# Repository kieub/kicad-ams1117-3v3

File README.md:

# AMS1117-3.3 Ultra-Compact LDO Power Module

KiCad를 활용하여 설계하고 JLCPCB를 통해 제작한 초소형 3.3V LDO 전원 레귤레이터 모듈입니다.  
5V~12V 입력을 받아 MCU, 센서 및 통신 모듈 구동에 필요한 저노이즈 3.3V 전원을 공급합니다.

---

## 1. 주요 사양 (Specifications)

| 항목 | 사양 (Specifications) | 비고 |
| :--- | :--- | :--- |
| **Topology** | Linear LDO Regulator | 저노이즈 3.3V 전원 출력 |
| **Input Voltage ($V_{in}$)** | DC 4.75V ~ 12V | 권장 입력 전압: 5V |
| **Output Voltage ($V_{out}$)** | DC 3.3V (±1.5%) | 고정 출력 (Fixed Output) |
| **Max Output Current ($I_{out}$)** | Max 800mA | 입력 전압 및 방열 조건에 따라 상이 |
| **PCB Dimensions** | 23.75 mm × 11.5 mm (1.6T) | 초소형 2-Layer FR-4 |
| **Surface Finish** | HASL (with lead) | 0805 수동 납땜성(Wettability) 최적화 |
| **Interface** | Wire Direct Soldering Pad | 실장 높이 최소화 및 기구 매립형 |

---

## 2. 부품 구성표 (BOM: Bill of Materials)

| Reference | Component / Part Number | Package | Description | Qty |
| :--- | :--- | :--- | :--- | :--- |
| **U1** | AMS1117-3.3V | SOT-223 | 3.3V 800mA LDO Regulator | 1 |
| **C1, C2** | 10µF / 25V (CL21A106KAFN3NE) | 0805 | 입·출력 평활 MLCC (DC 바이어스 마진 확보) | 2 |
| **R1** | 1kΩ ±1% 125mW (ERJ6ENF1001V) | 0805 | 상태 표시 LED 전류 제한 저항 | 1 |
| **D1** | Red-Orange SMD LED (599-0120-007F) | 0805 | 전원 인디케이터 LED ($I_f \approx 1.3\text{mA}$) | 1 |

---

## 3. 핵심 설계 포인트 (Engineering Points)

- **BOM 최적화 및 DC 바이어스 마진 확보**: 입·출력 평활 커패시터를 25V 내압의 10µF 0805 MLCC 1종으로 통합하여 자재 조달 효율을 극대화하고, DC 바이어스 전압 인가에 따른 실효 커패시턴스 감소 현상을 방지했습니다.
- **저전력 LED 회로 설계**: 3.3V 출력단에 1kΩ 저항을 직렬 매칭하여 약 1.3mA의 저전류 구동을 유도, 불필요한 대기 전력 소모와 눈부심을 줄였습니다.
- **방열 및 소형화 설계**: SOT-223 탭 하단에 넓은 구리 배선을 배치하여 열 방출 경로를 확보했으며, 커넥터 대신 와이어 직결 패드를 채택해 완제품 매립 시 부피를 최소화했습니다.

---

## 4. 디렉터리 구조 (Directory Structure)

```text
├── docs/               # 회로도, PCB 3D 렌더링, 실물 사진
├── gerber/             # JLCPCB 양산 발주용 거버 파일 (ZIP)
├── hardware/           # KiCad 프로젝트 파일 (.kicad_pro, .kicad_sch, .kicad_pcb)
└── README.md
```

---

## 5. 제작 및 검증 가이드 (Assembly & Verification)

### 5.1 실장 전 기판 검수 (Bare Board Inspection)
- **외관 검사**: 거버 파일과 실물 PCB를 대조하여 트레이스 단선, 비아 도금 상태, 솔더마스크 오픈 영역을 육안 점검합니다.
- **전원단 도통 검사**: 부품 실장 전 멀티미터 도통 모드로 $V_{in}\text{-}GND$ 및 $V_{out}\text{-}GND$ 간 단락(Short)이 없는지 확인합니다.

### 5.2 수동 SMD 납땜 (Hand Soldering)
간섭을 최소화하기 위해 **소형 수동 소자 $\rightarrow$ 대형 IC** 순서로 실장합니다.

| 순서 | 대상 부품 | 패키지 | 실장 요령 및 주의사항 |
| :---: | :--- | :--- | :--- |
| **1** | `R1` (1kΩ) | 0805 | 한쪽 패드 선납 후 핀셋으로 밀어 넣어 고정, 반대쪽 패드 납땜 |
| **2** | `C1, C2` (10µF) | 0805 | 극성이 없으므로 수평을 맞춰 대칭으로 실장 |
| **3** | `D1` (LED) | 0805 | 뒷면 캐소드(Cathode, $-$) 마킹 방향을 $GND$ 패드 쪽으로 정렬 |
| **4** | `U1` (AMS1117) | SOT-223 | Pin 1(GND) 가납으로 정렬 후 나머지 리드 납땜. 대형 방열 탭은 열을 충분히 가한 후 납 도포 |

### 5.3 전원 투입 및 성능 검증 (Power-on & Test)
1. **무부하 전압 측정**:
   - DC 파워서플라이를 **$5.0\text{V}$**, 전류 제한 **$100\text{mA}$**로 설정하여 인가합니다.
   - `D1` LED 정상 점등 여부와 출력단 전압을 멀티미터로 측정합니다.
   - **판정 기준**: $3.3\text{V} \pm 1.5\%$ ($3.25\text{V} \sim 3.35\text{V}$) 이내 유지 시 정상
2. **부하 테스트**:
   - 출력단에 부하 저항(약 $100\text{mA}$ 부하)을 연결하여 전압 강하(Load Regulation) 및 IC 발열을 모니터링합니다.

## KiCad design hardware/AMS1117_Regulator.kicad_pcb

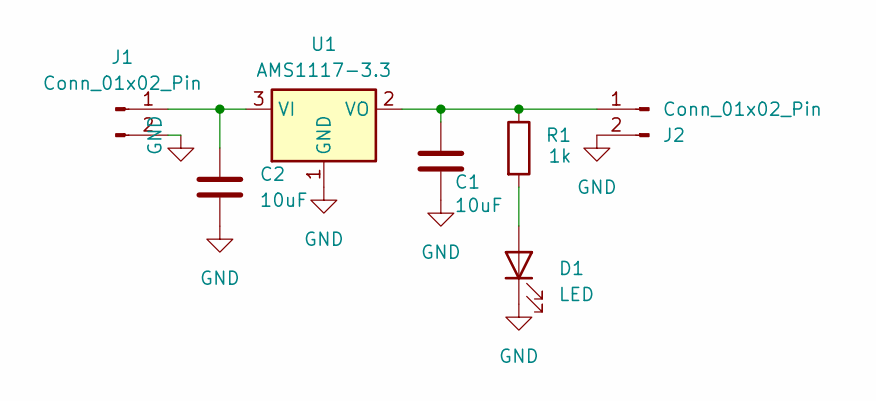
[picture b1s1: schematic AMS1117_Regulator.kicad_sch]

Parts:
C1, C2: 10uF; C_0805_2012Metric
D1: LED; LED_0805_2012Metric
J1, J2: Conn_01x02_Pin; PinHeader_1x02_P2.54mm_Vertical
R1: 1k; R_0805_2012Metric
U1: AMS1117-3.3; SOT-223-3_TabPin2

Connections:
GND: C1.2, C2.2, D1.1 (K), J1.2, J2.2, U1.1 (GND)
unnamed: D1.2 (A), R1.2
unnamed: C2.1, J1.1, U1.3 (VI)
unnamed: C1.1, J2.1, R1.1, U1.2 (VO)

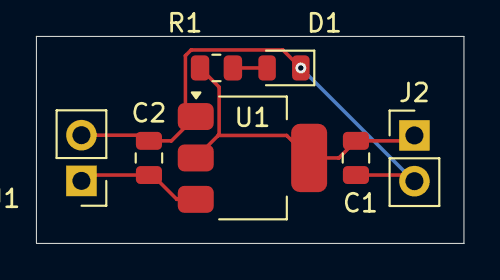
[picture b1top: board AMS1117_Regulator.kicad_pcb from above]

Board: 2 copper layers, 23.8 x 11.5 mm, 7 parts (0 on the bottom side), 4 nets.
